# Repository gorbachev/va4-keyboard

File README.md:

# The DIY Keyboard `va4` (v0.4.x)

`va4` the 4x2 key split keyboard.

**`OEM Profile Keycaps` + `CherryMX Compatible Switch`** version: (`v0.3.0`)

**`G20 Profile Keycaps` + `CherryMX Compatible Switch`** version: (`v0.2.0`)

**`Kailh Choc(Low profile)` Key Switch** version: (`v0.2.0`)

## Features

* 🕹 Support for Rotary Encoder in v0.4

* ⌨️ Support `Cherry MX Compatible Switch` and `Kailh Low Profile Choc Switch`

* 🖥️ Support `Pro Micro` compatible board

* 🔑 Password writing space

* 🥚 Columbus' egg included

* 📜 Open Source License

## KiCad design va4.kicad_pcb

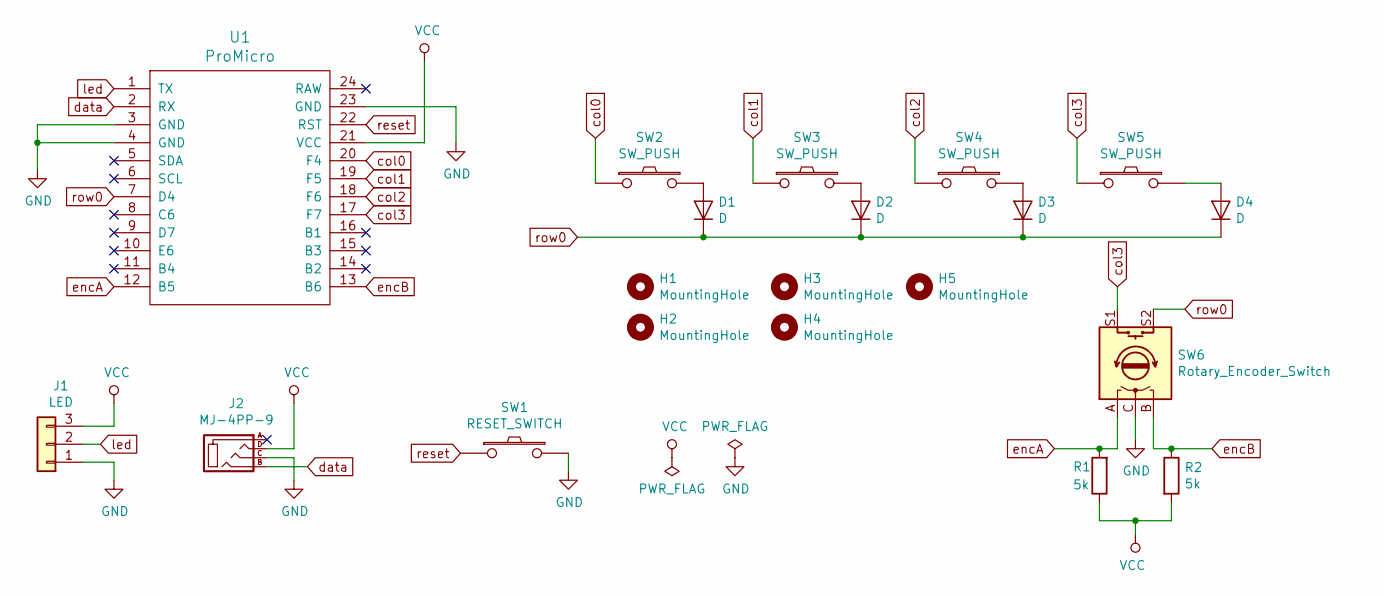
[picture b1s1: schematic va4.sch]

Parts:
D1, D2, D3, D4: D; D3_TH_SMD
H1, H2, H3, H4, H5: MountingHole; HOLE
J1: LED; StripLED_rev
J2: MJ-4PP-9
R1, R2: 5k; 0805
SW1: RESET_SWITCH; ResetSW
SW2, SW3, SW4: SW_PUSH; MX_ALPS_PG1350_noLed
SW5: SW_PUSH; MX_reversible
SW6: Rotary_Encoder_Switch; ALPS_EC11E
U1: ProMicro; ProMicro_v2

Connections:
GND: J1.1, J2.C, SW1.2, SW6.C, U1.3 (GND), U1.4 (GND), U1.23 (GND)
unnamed: D1.2 (A), SW2.2
unnamed: D2.2 (A), SW3.2
unnamed: D3.2 (A), SW4.2
unnamed: D4.2 (A), SW5.2
VCC: J1.3, J2.D, R1.1, R2.2, U1.21 (VCC)
col0: SW2.1, U1.20 (F4)
col1: SW3.1, U1.19 (F5)
col2: SW4.1, U1.18 (F6)
col3: SW5.1, SW6.S1, U1.17 (F7)
data: J2.B, U1.2 (RX)
encA: R1.2, SW6.A, U1.12 (B5)
encB: R2.1, SW6.B, U1.13 (B6)
led: J1.2, U1.1 (TX)
reset: SW1.1, U1.22 (RST)
row0: D1.1 (K), D2.1 (K), D3.1 (K), D4.1 (K), SW6.S2, U1.7 (D4)

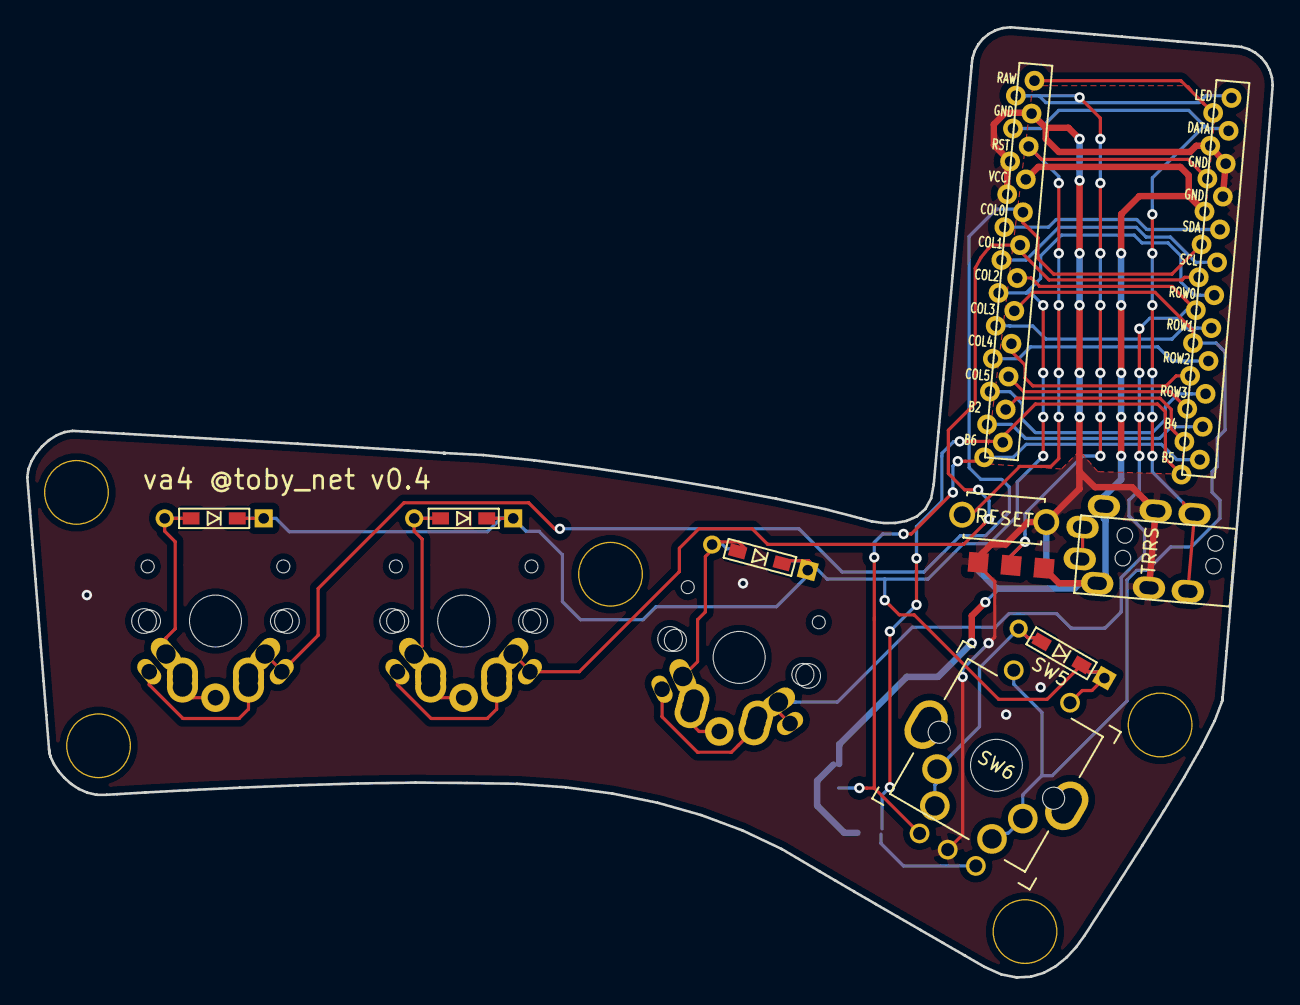
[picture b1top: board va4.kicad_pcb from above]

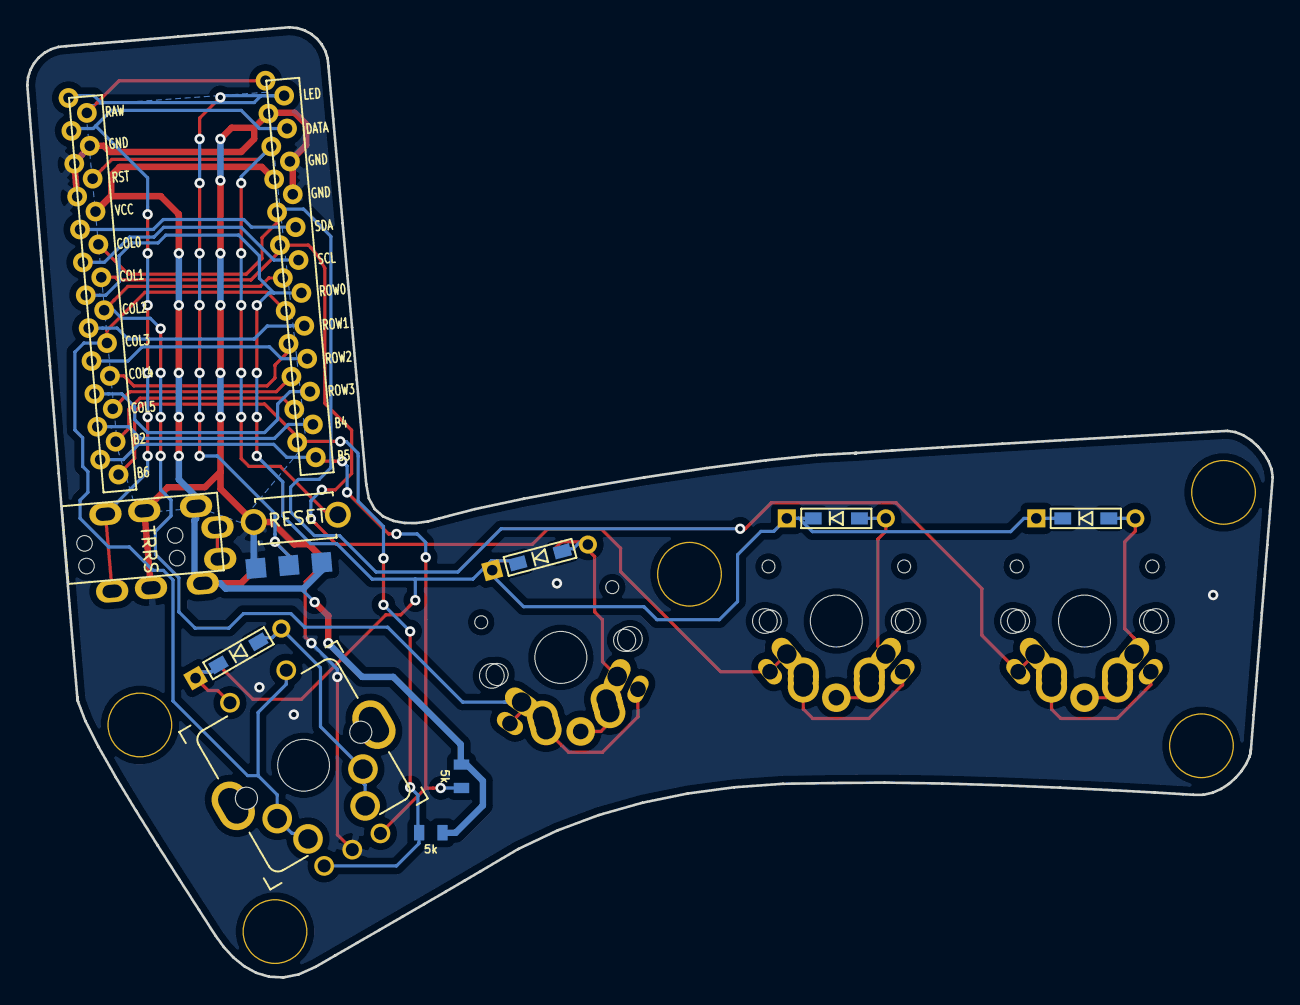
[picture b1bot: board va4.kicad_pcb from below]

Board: 2 copper layers, 95.8 x 73.1 mm, 20 parts (2 on the bottom side), 16 nets.

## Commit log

2019-09-04 Rotary encoder with mx SW5
2019-09-04 choc mx hybrid with rotary encoder on SW5
2019-09-04 Fix D4 front pad
2019-09-04 Add logos back in
2019-09-04 mention rotary encoder support in README.md
2020-05-17 Encoder support v0.4
